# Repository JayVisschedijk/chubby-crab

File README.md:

# Chubby Crab (Colorlight Programmer)
A project to make programming the Colorlight 5A-75B a plug-and-play situation. It is built around the Adafruit FT232H.  
This programmer only fits on Colorlight 5A-75B versions 8.x

This project is inspired by the [q3k/chubby75](https://github.com/q3k/chubby75) project.  
Placement of the components is taken from [cyber-murmel/chubby-hat](https://github.com/cyber-murmel/chubby-hat). Thank you for doing the work of mapping the exact placements.

# How to use
*Note: if you're looking for a quick and easy way to flash just a few Colorlights, you might as well just use a JTAG programmer and connect it as explained in the [chubby75 documentation](https://github.com/q3k/chubby75/tree/master/5a-75b).*

Connect the Chubby Crab to the Colorlight by placing the 4 connectors (arms and legs) on Colorlight connectors J3, J4, J5, J6. When placed correctly, the pogo pins will connect to the JTAG, 3.3V, GND pads on the Colorlight.
When powering the Colorlight via the Chubby Crab (USB), set the slide switch to 3.3V. When powering the Colorlight with external 5V, set the slide switch to NC (Not Connected).

# Make your own
This repo contains all files to make your own Chubby Crab. Follow the steps from `./instructions.md` and you should end up with your own crab.
For those that skip instruction files: J7 parts are not included in the BOM, order separately.

## Room for improvement
This was just my first prototype and since it does what it must do, I can't be bothered (yet) to make a V2. But there's (quite some) room for improvement. Please open issues for ideas for improvement. If the list grows big enough, I might make a V2.

# License
This project is released under the MIT license.
Note that a part of this project was taken from the [cyber-murmel/chubby-hat](https://github.com/cyber-murmel/chubby-hat) project under [MIT License](https://github.com/cyber-murmel/chubby-hat/blob/main/LICENSE).

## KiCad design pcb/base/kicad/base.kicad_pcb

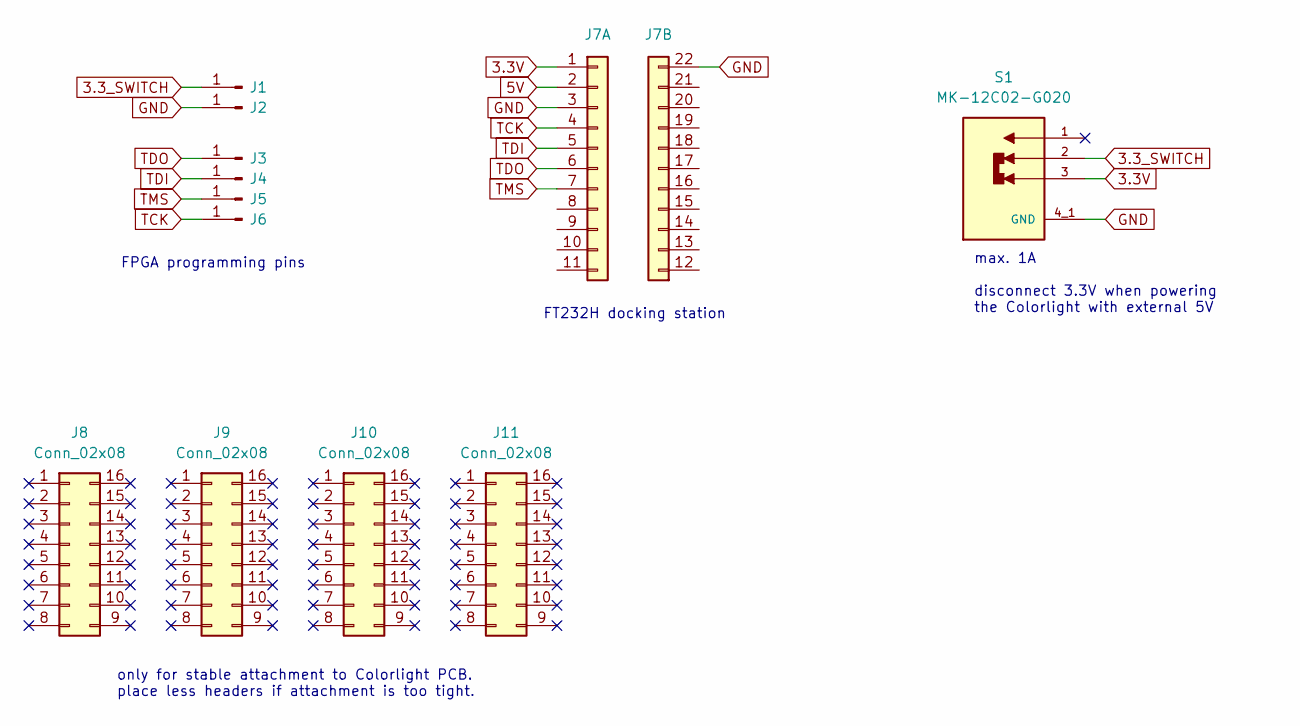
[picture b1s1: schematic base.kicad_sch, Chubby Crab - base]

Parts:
J1, J2, J3, J4, J5, J6: Conn_01x01_Pin; PogoPin_0.9mm_ThroughHole; LCSC Part # C7471744
J7: FT232H_2x11_P2.54mm
J8, J9, J10, J11: Conn_02x08; PinSocket_2x08_P2.54mm_Vertical; LCSC Part # C30734
S1: MK-12C02-G020; SW_MSK12C02; Mf. Part # MK-12C02-G020; LCSC Part # C963206

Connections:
3.3V: J7.1, S1.3
3.3_SWITCH: J1.1, S1.2
5V: J7.2
GND: J2.1, J7.3, J7.22, S1.4_1 (GND), S1.4_2 (GND), S1.4_3 (GND), S1.4_4 (GND)
TCK: J6.1, J7.4
TDI: J4.1, J7.5
TDO: J3.1, J7.6
TMS: J5.1, J7.7

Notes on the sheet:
only for stable attachment to Colorlight PCB. place less headers if attachment is too tight.
max. 1A disconnect 3.3V when powering the Colorlight with external 5V
FPGA programming pins
FT232H docking station

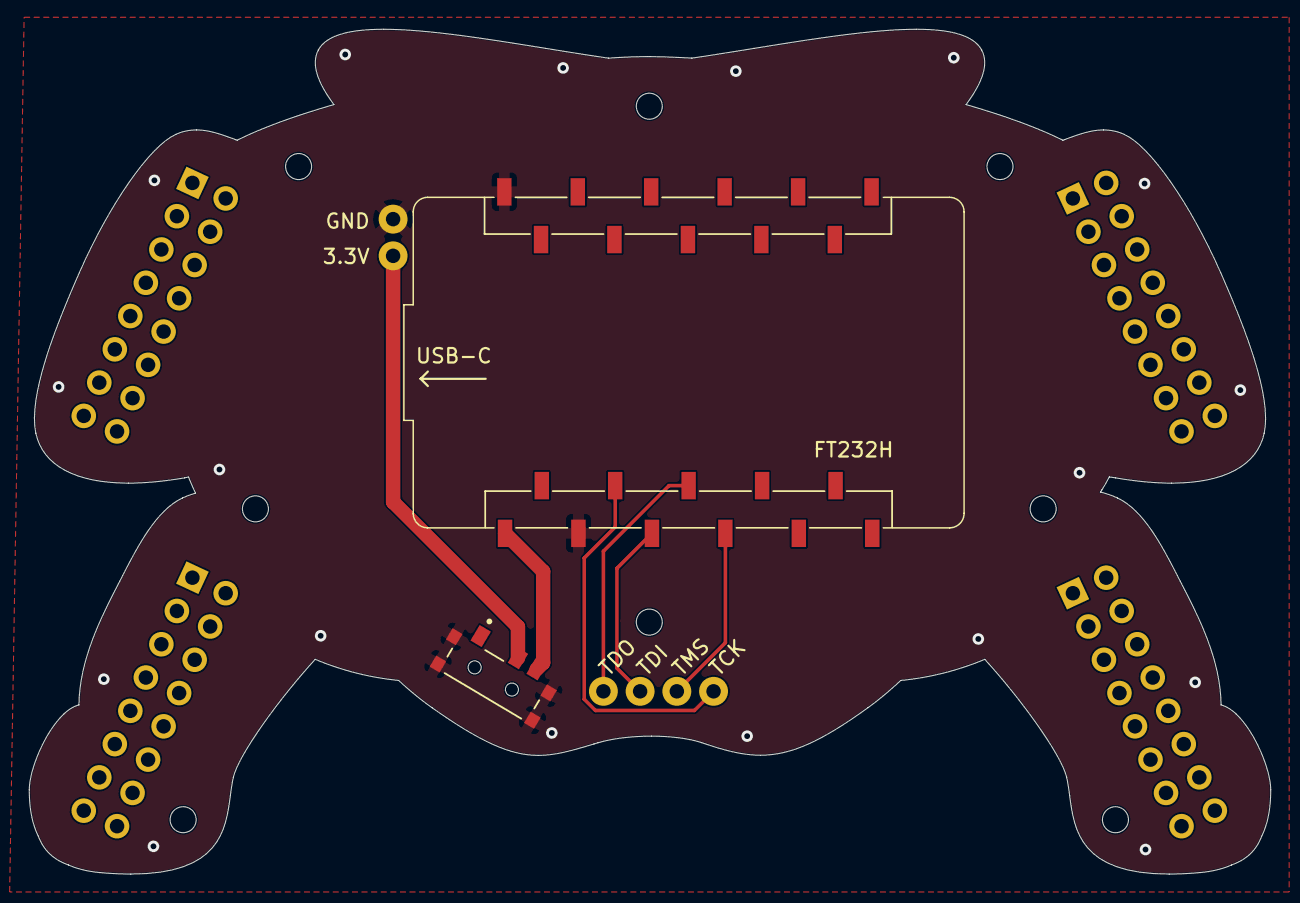
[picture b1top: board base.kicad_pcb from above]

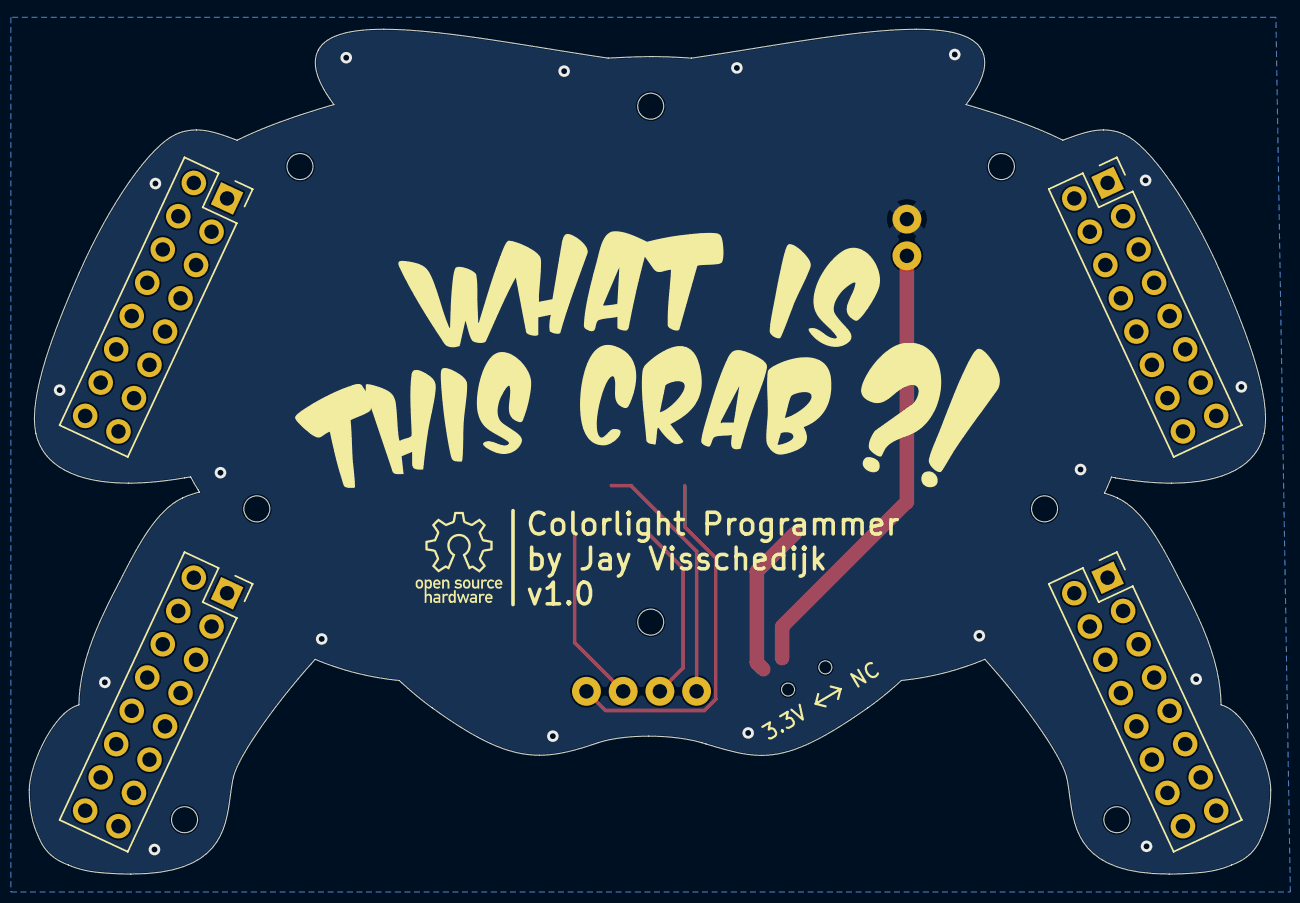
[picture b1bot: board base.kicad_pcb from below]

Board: 2 copper layers, 85.9 x 58.4 mm, 20 parts (18 on the bottom side), 7 nets.

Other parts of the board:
H1, H2, H3, H4, H5, H6, H7, H8: MountingHole; MountingHole_1.8mm_M1.6

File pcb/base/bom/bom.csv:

Designator,Footprint,Qty,Value,LCSC Part #
"J1,J2,J3,J4,J5,J6",ChubbyCrab:PogoPin_0.9mm_ThroughHole,6,Conn_01x01_Pin,C7471744
"J8,J9,J10,J11",Connector_PinSocket_2.54mm:PinSocket_2x08_P2.54mm_Vertical,4,Conn_02x08,C30734
S1,ChubbyCrab:SW_MSK12C02,1,MK-12C02-G020,C963206
